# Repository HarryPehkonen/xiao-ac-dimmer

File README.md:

# xiao-ac-dimmer

One-channel inline AC dimmer for a Seeed Studio XIAO ESP32C3 (or any XIAO on the
same 14-pad footprint). Mains cord in one end, lamp socket out the other, and the
triac dims whatever is plugged in between them. Plug-in bench/room scale — not
house wiring.

**Status: generated schematic and PCB, both machine-checked. The board is
150 × 57 mm (85.5 cm²), 16/16 nets routed, DRC clean — 0 errors, 0 warnings.**

## The schematic is generated

`xiao-ac-dimmer.kicad_sch` is written by `tools/gen_sch.py`. The circuit lives
there as a table of parts and nets; the generator draws each symbol, a stub wire
per pin and a label naming that pin's net. Open the result in KiCad 9 to review
it like any other schematic.

That indirection is deliberate: a hand-drawn schematic cannot be verified, and
a generated one can (see Gates).

## Gates

```sh
./tools/ci.sh
```

1. **Generator == committed file.** Regenerating leaves `xiao-ac-dimmer.kicad_sch`
   and `symbols/xiao-ac.kicad_sym` byte-identical, so neither the committed
   schematic nor the symbol library it draws `J1`/`J2` from is ever stale.
2. **Netlist == intent.** `tools/check_netlist.py` exports a netlist with
   `kicad-cli` and asserts it against the intended netlist: every net present
   with exactly the intended pins, no unintended net at all (that would be a
   short), only the deliberately open pins reported unconnected, and every pin
   of the two XIAO socket rows carrying the *module's* pin name — `D0..D6` on
   `J1`, `VBUS, GND, 3V3_OUT, D10, D9/BOOT, D8, D7` on `J2` — so the schematic
   and its netlist say which pin is which instead of leaving it to a comment.
   This gate caught a rotated-symbol pin swap that would have fitted the
   Schottky diode backwards.
3. **ERC clean.** `kicad-cli sch erc` reports 0 violations.
4. **Board DRC clean.** `tools/check_board.py` — 0 errors, 0 warnings, including
   the 3 mm mains/logic clearance rule in `xiao-ac-dimmer.kicad_dru`. The same
   check asserts the rules DRC has no rule for: every footprint id names its
   library, the four M3 mounting holes are where the design says with an empty
   6 mm copper keepout, and the two socket rows are one mating interface that a
   XIAO actually fits (15.24 mm apart — the defect that got through ERC, DRC,
   the netlist and the router).
5. **Board == generator.** `tools/check_regen.py` regenerates the board in a
   throwaway copy of the tools and compares every footprint and every copper
   item against the committed board — 24 footprints (20 parts + 4 mounting
   holes) and 502 tracks+vias today.
   The board file is not *byte*-reproducible (pcbnew stamps fresh UUIDs and
   writes items in its own order), so this compares geometry, which is the part
   a person would have had to edit. `docs/PCB-NOTES.md` has the measurement and
   the two sabotage runs.
6. **The gates' own tests.** `tools/tests/test_board_gate.py` breaks every rule
   check 4 enforces — all three families, on a copy of the committed board — and
   asserts `check_board.py` reports each one by name. The socket: rows too
   close, a pin that is not in the row, an extra pin, a reversed row, a row
   renumbered, a part inside the module envelope, the wrong pitch, a hole too
   small for a module pin, a row out of the group, a missing group, an unlocked
   row, swapped rows, a missing or moved envelope, the trigger on the wrong pin,
   a socket that is not a socket (no through-hole pad). The library nicknames: a
   footprint id with no nickname, and the 24 nicknamed ids the board has to
   carry. The mounting holes: one moved, one renamed, one missing, a track and a
   pad inside the keepout, a hole tied to a net, a plated hole, a hole drilled
   too small. Each case has also been seen to fail with the rule it targets
   removed from `check_board.py`, so none of them passes by accident —
   `docs/PCB-NOTES.md`, "What the gate's tests have been seen to do".
   Then the router's ordering and retry
   (`test_a_rerouted_board_is_still_clean` puts the retry through DRC, which
   would not have noticed it).
   `tools/tests/test_pin_names.py` covers check 2's pin names: a renamed pin, the
   rows back to `Pin_1..Pin_7`, a renumbered row. `test_board_routes.py`
   regenerates and runs DRC; `test_route_geometry.py` and `test_route_open.py`
   pin the router's geometry and its off-grid edge case. A rule that has never
   been seen to fail is not a gate.

## Circuit in one paragraph

Cord hot goes through a 3.15 A fuse, then feeds an MOV, the HLK-PM01's AC input
and the triac's A1; neutral runs straight through to the outlet, unswitched.
The HLK's isolated 5 V reaches the XIAO's VBUS pad through a Schottky diode. An
H11AA1 across the mains (47 k in each leg) pulls D2 low at every zero crossing;
firmware then fires the MOC3021 random-phase opto from D1 through 220 Ω, which
triggers the BTA16-600B through 1 k, with a 100 Ω + 100 nF snubber across it.
Part-by-part reasoning, including what is deliberately *not* proven: DESIGN.md.

## Bill of materials (all through-hole)

| Ref | Part | Note |
| --- | --- | --- |
| PS1 | HLK-PM01 | isolated 100–240 VAC → 5 V 0.6 A |
| F1 | 5×20 mm fuse clip + 3.15 A slow-blow | hot leg only |
| MOV1 | S14K150 varistor | 150 VAC rating |
| Q1 | BTA16-600B | TO-220, small heatsink |
| U2 | MOC3021M | *random-phase* opto-triac, DIP-6 |
| U1 | H11AA1 | AC-input optocoupler, DIP-6 |
| D5 | SS14 | Schottky, VBUS feed |
| R1, R2 | 47 k 1/4 W | ZCD legs (≈1.3 mA rms each) |
| R3 | 220 Ω | MOC LED from 3.3 V (≈9 mA) |
| R4 | 1 k | triac gate |
| R5 | 10 k | ZCD pull-up to 3V3 |
| RS1 | 100 Ω | snubber |
| C1 | 470 µF 16 V | 5 V bulk |
| C2 | 100 nF | XIAO decoupling |
| CS1 | 100 nF 400 V film | snubber |
| J1, J2 | 2 × 1×07 2.54 mm socket | XIAO: J1 = D0..D6, J2 = 5V..D7 |
| J3, J4 | 2-pole 5.08 mm screw terminal | cord in / lamp out |

## Safety — read before powering anything up

- The hot is switched and fused; the neutral is never broken and never fused
  on its own.
- Never work on it live. First power-up on a GFCI/RCD outlet. **Never flash
  firmware with mains connected.**
- The layout slice will enforce ≥3 mm clearance across the barrier with a
  routed isolation slot. Do not shrink it to make the board smaller.
- 3.15 A suits a ~60 W lamp. A larger load needs the fuse, the copper and the
  triac's heatsinking rechecked.
- Only dimmable LED bulbs dim; some need a bleeder, some buzz, some refuse
  below ~20 %. That is measured on the bench, not simulated.
- Nothing here is a safety certification. The insulation barrier is the
  HLK-PM01, the optos and the layout, and the enclosure is yours.

## Files

```
xiao-ac-dimmer.kicad_sch   generated schematic (the reviewable design)
xiao-ac-dimmer.kicad_pcb   generated board -- never hand-edit
xiao-ac-dimmer.kicad_dru   the 3 mm mains/logic barrier and the 1 mm mains width
xiao-ac-dimmer.kicad_pro   project + netclass settings
symbols/xiao-ac.kicad_sym  the socket rows' symbols, pins named D0..D6 / VBUS..D7
sym-lib-table fp-lib-table so the libraries resolve without global config
tools/kicadlib.py          s-expression reader, symbol flattening (extends)
tools/gen_sch.py           the circuit + schematic generator
tools/gen_pcb.py           placement + board generator
tools/route.py             the maze router
tools/check_netlist.py     gate: exported netlist == intended netlist (and pin names)
tools/check_board.py       gate: kicad-cli pcb drc + the rules DRC cannot express
tools/check_regen.py       gate: committed board == generated board (geometry)
tools/ci.sh                the gate
tools/probe_libs.py        diagnostic: does each embedded symbol load?
tools/tests/               the gates' own tests (every rule, seen to fail)
sim/                       ngspice decks and measured results
docs/PCB-NOTES.md          board status, and what the router needed
DESIGN.md                  engineering decisions and open items
BOM.md                     sourcing and mechanical notes
```

## Requirements

KiCad 9 (`kicad-cli`) and ngspice 44:

```sh
sudo apt-get install kicad kicad-symbols kicad-footprints ngspice
```

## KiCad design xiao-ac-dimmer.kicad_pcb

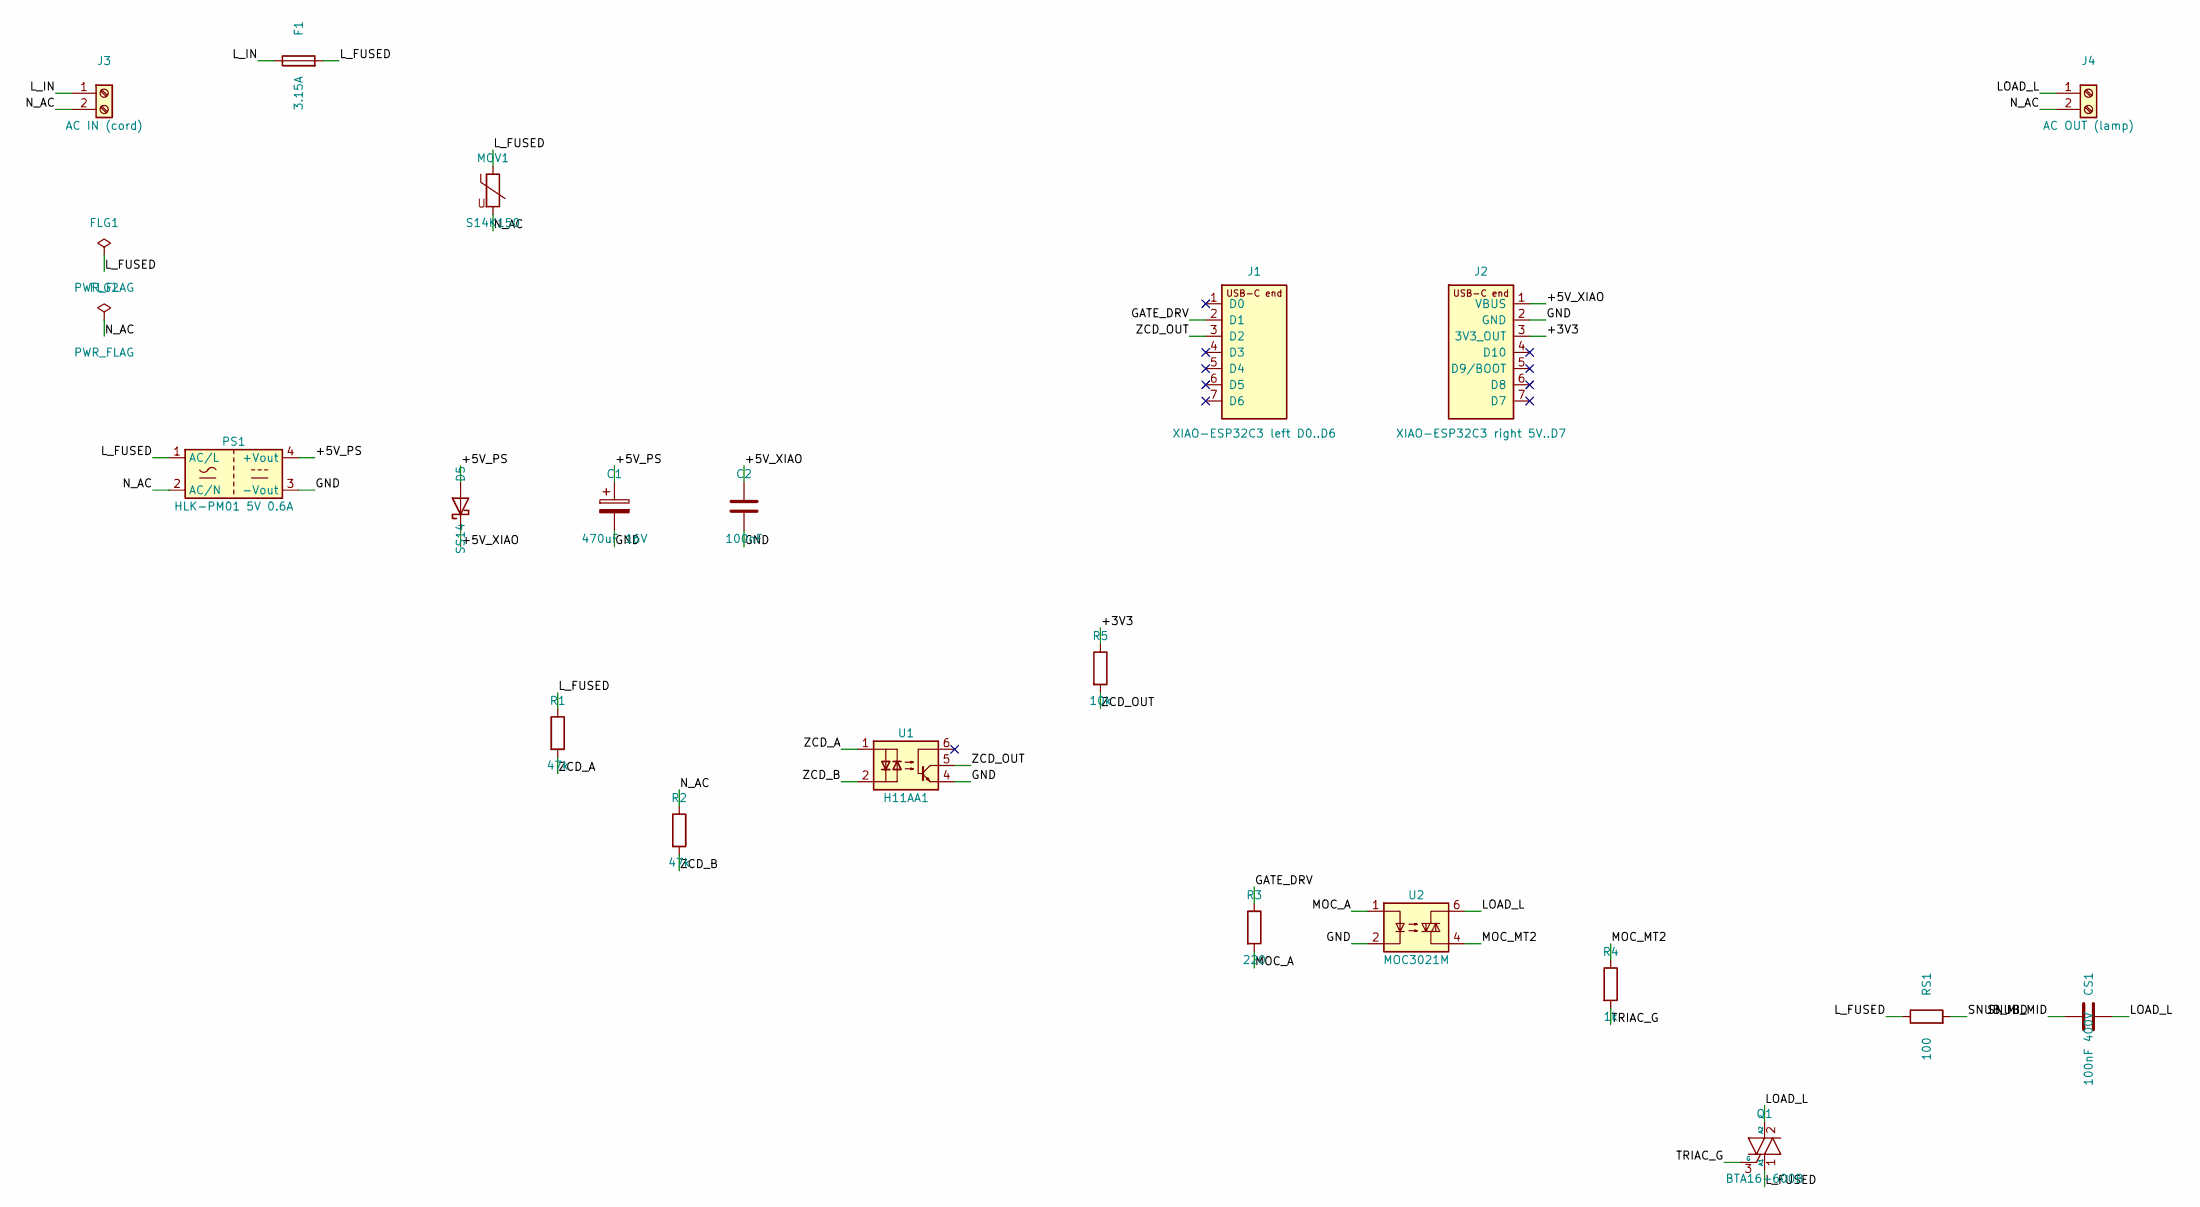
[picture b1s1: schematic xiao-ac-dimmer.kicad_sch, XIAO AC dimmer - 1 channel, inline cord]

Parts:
C1: 470uF 16V; CP_Radial_D8.0mm_P3.50mm
C2: 100nF; C_Disc_D5.0mm_W2.5mm_P5.00mm
CS1: 100nF 400V; C_Rect_L7.0mm_W2.0mm_P5.00mm
D5: SS14; D_DO-41_SOD81_P10.16mm_Horizontal
F1: 3.15A; Fuseholder_Clip-5x20mm_Keystone_3512P_Inline_P23.62x7.27mm_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
FLG1, FLG2: PWR_FLAG
J1: XIAO-ESP32C3 left D0..D6; PinSocket_1x07_P2.54mm_Vertical
J2: XIAO-ESP32C3 right 5V..D7; PinSocket_1x07_P2.54mm_Vertical
J3: AC IN (cord); TerminalBlock_Phoenix_MKDS-1,5-2-5.08_1x02_P5.08mm_Horizont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
J4: AC OUT (lamp); TerminalBlock_Phoenix_MKDS-1,5-2-5.08_1x02_P5.08mm_Horizont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
MOV1: S14K150; RV_Disc_D12mm_W4.5mm_P7.5mm
PS1: HLK-PM01 5V 0.6A; Converter_ACDC_Hi-Link_HLK-PMxx
Q1: BTA16-600B; TO-220-3_Vertical
R1, R2: 47k; R_Axial_DIN0207_L6.3mm_D2.5mm_P10.16mm_Horizontal
R3: 220; R_Axial_DIN0207_L6.3mm_D2.5mm_P10.16mm_Horizontal
R4: 1k; R_Axial_DIN0207_L6.3mm_D2.5mm_P10.16mm_Horizontal
R5: 10k; R_Axial_DIN0207_L6.3mm_D2.5mm_P10.16mm_Horizontal
RS1: 100; R_Axial_DIN0207_L6.3mm_D2.5mm_P10.16mm_Horizontal
U1: H11AA1; DIP-6_W7.62mm
U2: MOC3021M; DIP-6_W7.62mm

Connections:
+3V3: J2.3 (3V3_OUT), R5.1
+5V_PS: C1.1, D5.2 (A), PS1.4 (+Vout)
+5V_XIAO: C2.1, D5.1 (K), J2.1 (VBUS)
GATE_DRV: J1.2 (D1), R3.1
GND: C1.2, C2.2, J2.2 (GND), PS1.3 (-Vout), U1.4, U2.2
LOAD_L: CS1.2, J4.1, Q1.2 (A2), U2.6
L_FUSED: F1.2, FLG1.1, MOV1.1, PS1.1 (AC/L), Q1.1 (A1), R1.1, RS1.1
L_IN: F1.1, J3.1
MOC_A: R3.2, U2.1
MOC_MT2: R4.1, U2.4
N_AC: FLG2.1, J3.2, J4.2, MOV1.2, PS1.2 (AC/N), R2.1
SNUB_MID: CS1.1, RS1.2
TRIAC_G: Q1.3 (G), R4.2
ZCD_A: R1.2, U1.1
ZCD_B: R2.2, U1.2
ZCD_OUT: J1.3 (D2), R5.2, U1.5

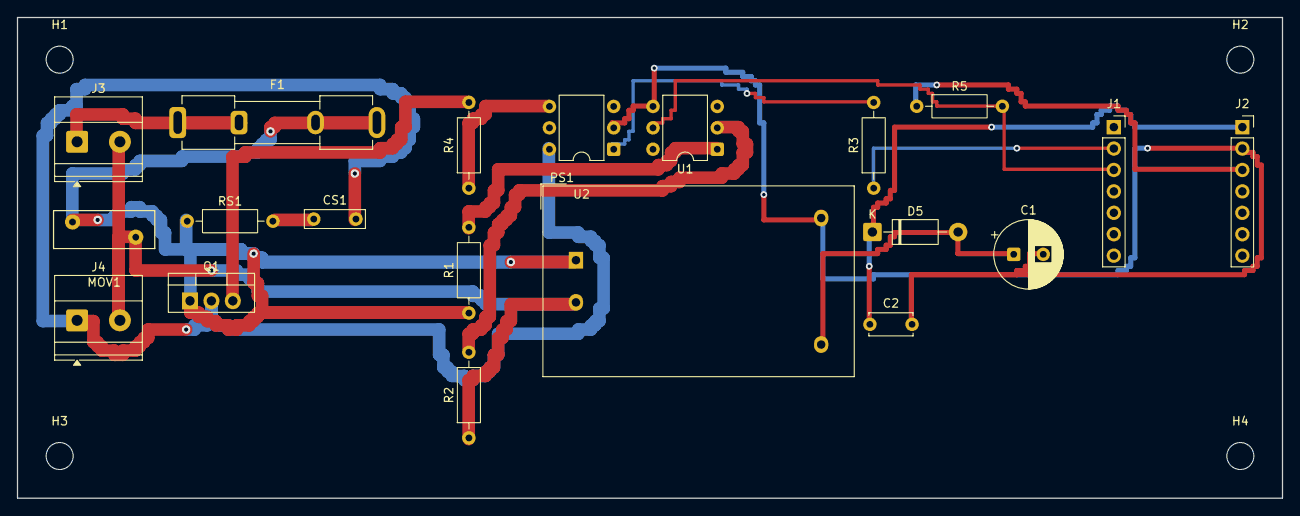
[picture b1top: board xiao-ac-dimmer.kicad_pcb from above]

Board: 2 copper layers, 150.0 x 57.0 mm, 24 parts (0 on the bottom side), 16 nets.

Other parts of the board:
H1, H2, H3, H4: MountingHole_3.2mm_M3

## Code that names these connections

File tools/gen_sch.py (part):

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PARTS = [
    # mains inlet, protection, isolated supply
    {"ref": "J3", "lib": "Connector:Screw_Terminal_01x02", "val": "AC IN (cord)",
     "fp": TERM, "at": (40, 60, 0), "pins": {"1": "L_IN", "2": "N_AC"}},
    {"ref": "F1", "lib": "Device:Fuse", "val": "3.15A", "fp": FUSEHLD,
     "at": (70, 55, 90), "pins": {"1": "L_IN", "2": "L_FUSED"}},
    {"ref": "MOV1", "lib": "Device:Varistor", "val": "S14K150",
     "fp": "Varistor:RV_Disc_D12mm_W4.5mm_P7.5mm", "at": (100, 75, 0),
     "pins": {"1": "L_FUSED", "2": "N_AC"}},
    {"ref": "PS1", "lib": "Converter_ACDC:HLK-PM01", "val": "HLK-PM01 5V 0.6A",
     "fp": "Converter_ACDC:Converter_ACDC_Hi-Link_HLK-PMxx", "at": (60, 120, 0),
     "pins": {"1": "L_FUSED", "2": "N_AC", "3": "GND", "4": "+5V_PS"}},
    # Schottky: Seeed require a diode between an external 5V source and VBUS
    {"ref": "D5", "lib": "Device:D_Schottky", "val": "SS14",
     "fp": "Diode_THT:D_DO-41_SOD81_P10.16mm_Horizontal", "at": (95, 125, 90),
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     "pins": {"1": "+5V_XIAO", "2": "GND"}},
    # zero-cross detector: one 47k in each leg, H11AA1 across the mains
    {"ref": "R1", "lib": "Device:R", "val": "47k", "fp": R_AX,
     "at": (110, 160, 0), "pins": {"1": "L_FUSED", "2": "ZCD_A"}},
    {"ref": "R2", "lib": "Device:R", "val": "47k", "fp": R_AX,
     "at": (130, 175, 0), "pins": {"1": "N_AC", "2": "ZCD_B"}},
    {"ref": "U1", "lib": "Isolator:H11AA1", "val": "H11AA1", "fp": DIP6,
     "at": (165, 165, 0),
     "pins": {"1": "ZCD_A", "2": "ZCD_B", "4": "GND", "5": "ZCD_OUT", "6": "NO"}},
    {"ref": "R5", "lib": "Device:R", "val": "10k", "fp": R_AX,
     "at": (195, 150, 0), "pins": {"1": "+3V3", "2": "ZCD_OUT"}},
    # XIAO sockets.  LEFT top->bottom = D0..D6 ; RIGHT top->bottom = 5V, GND,
    # 3V3, D10, D9, D8, D7 (Seeed front pinout diagram) -- the names come from
    # XIAO_ROWS above, so the symbol says it and the netlist carries it.
    {"ref": "J1", "lib": SYMLIB + ":XIAO_ESP32C3_Left", "val": XIAO_ROWS[0]["value"],
     "fp": SOCK7, "at": (220, 100, 0), "pins": {"2": "GATE_DRV", "3": "ZCD_OUT"},
     "nc": ["1", "4", "5", "6", "7"], "ref_dy": -12.7, "val_dy": 12.7},
    {"ref": "J2", "lib": SYMLIB + ":XIAO_ESP32C3_Right", "val": XIAO_ROWS[1]["value"],
     "fp": SOCK7, "at": (255, 100, 0), "pins": {"1": "+5V_XIAO", "2": "GND", "3": "+3V3"},
     "nc": ["4", "5", "6", "7"], "ref_dy": -12.7, "val_dy": 12.7},
    # trigger: GPIO3 (D1) -> 220R -> MOC3021 LED ; MOC output drives the gate
    {"ref": "R3", "lib": "Device:R", "val": "220", "fp": R_AX,
     "at": (220, 190, 0), "pins": {"1": "GATE_DRV", "2": "MOC_A"}},
    {"ref": "U2", "lib": "Relay_SolidState:MOC3021M", "val": "MOC3021M", "fp": DIP6,
     "at": (245, 190, 0),
     "pins": {"1": "MOC_A", "2": "GND", "4": "MOC_MT2", "6": "LOAD_L"}},
    {"ref": "R4", "lib": "Device:R", "val": "1k", "fp": R_AX,
     "at": (275, 200, 0), "pins": {"1": "MOC_MT2", "2": "TRIAC_G"}},
    {"ref": "Q1", "lib": "Triac_Thyristor:BTA16-600B", "val": "BTA16-600B",
     "fp": "Package_TO_SOT_THT:TO-220-3_Vertical", "at": (300, 225, 0),
     "pins": {"1": "L_FUSED", "2": "LOAD_L", "3": "TRIAC_G"}},
    {"ref": "RS1", "lib": "Device:R", "val": "100", "fp": R_AX,
     "at": (325, 205, 90), "pins": {"1": "L_FUSED", "2": "SNUB_MID"}},
    {"ref": "CS1", "lib": "Device:C", "val": "100nF 400V",
     "fp": "Capacitor_THT:C_Rect_L7.0mm_W2.0mm_P5.00mm", "at": (350, 205, 90),
     "pins": {"1": "SNUB_MID", "2": "LOAD_L"}},
    # mains outlet (lamp), neutral unswitched
    {"ref": "J4", "lib": "Connector:Screw_Terminal_01x02", "val": "AC OUT (lamp)",
     "fp": TERM, "at": (350, 60, 0), "pins": {"1": "LOAD_L", "2": "N_AC"}},
    # ERC: L_IN and N_AC are fed by a passive terminal block
    {"ref": "FLG1", "lib": "power:PWR_FLAG", "val": "PWR_FLAG", "fp": "",
     "at": (40, 85, 0), "pins": {"1": "L_FUSED"}},
    {"ref": "FLG2", "lib": "power:PWR_FLAG", "val": "PWR_FLAG", "fp": "",
     "at": (40, 95, 0), "pins": {"1": "N_AC"}},
]


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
